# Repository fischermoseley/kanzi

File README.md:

# kanzi
A two wheeled, self balancing skateboard made for a final project in MIT's 6.1311 Power Electronics Laboratory class. Named after Kanzi the Bonobo, because Bonobos are dope.

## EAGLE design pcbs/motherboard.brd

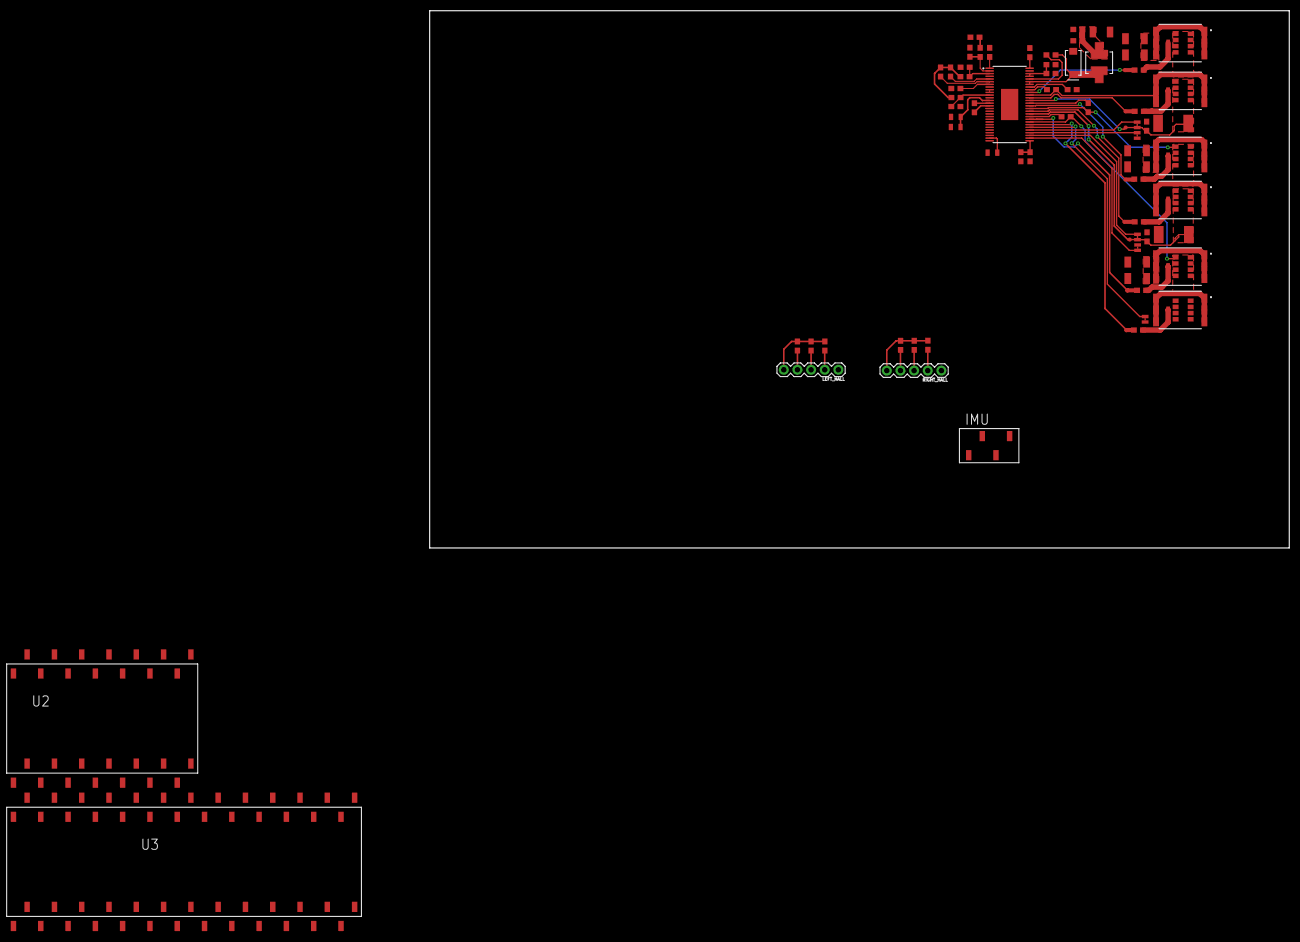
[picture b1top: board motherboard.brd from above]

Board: 2 copper layers, 160.0 x 100.0 mm, 77 parts (0 on the bottom side), 71 nets.

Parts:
C1, C2, C3, C4, C5, C6: 4.7uF 100V; 1210
C7, C8: 1nF; 0603
C9: 6.8nF; 0603
C10: 120pF; 0603
C11, C12, C14: 2.2uF; 0805
C13: 22nF 36V; 0603
C15, C17, C23: 4.7uF; 0603
C16, C18, C19, C20, C21, C22, C24: 0.1uF; 0603
C25: 100uF; 1210
C26: 15nF; 0603
D1: NRVBA2H100T3G; SMA-DIODE
IMU: SSM-104-L-SV; SAMTEC-SSM-104-X-SV
JP1, JP2, JP3, JP4, JP5: JUMPER-SMT_2_NC_TRACE_NO-SILK; SMT-JUMPER_2_NC_TRACE_NO-SILK
L1: 22uH; LQH43
LEFT_HALL: 1X05
R1, R2, R3, R4, R5, R6: 4.7R; 0603
R7, R8: 10mOhm; R2512
R9, R10, R11, R12, R13, R14, R17, R18, R19, R20, R21: 10k; 0603
R15: 200k; 0603
R16: 16.2k; 0603
R22: OPEN; 0603
R23: SHORT; 0603
R24: 1M; 0603
RIGHT_HALL: 1X05
TP1, TP2, TP3, TP4, TP5, TP6, TP7, TP8: TEST-POINT3; PAD.03X.03
U1: DRV8302DCAR; SOP50P810X120-57N
U2: TEENSY3.2
U3: PSOC5LP
U4, U5, U6, U7\, U8, U9: IRF7749L; TRANS_AUIRF8739L2TR

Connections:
+3V3: IMU.3, U2.26
+5V: LEFT_HALL.5, R9.2, R10.2, R11.2, R12.2, R13.2, R14.2, R18.2, R19.2, R20.2, R22.2, RIGHT_HALL.5, U1.9, U1.10, U1.24, U2.28
AGND: C1.2, C2.2, C3.2, C4.2, C5.2, C6.2, C7.2, C8.2, JP2.2, JP4.2, JP5.2, R7.2, R8.2, U9.4, U9.5, U9.6, U9.7, U9.8, U9.9, U9.10, U9.11
DGND: C9.1, C10.1, C11.2, C12.2, C14.2, C15.2, C16.2, C17.2, C18.2, C23.2, C24.2, C25.2, C26.1, D1.A, IMU.4, LEFT_HALL.1, R15.2, R17.1, R21.1, R24.2, RIGHT_HALL.1, U1.8, U1.28, U1.57, U2.1, U3.1, U3.25, U3.51
ENABLE: U1.16, U2.15
GH_A: R1.1, TP1.P$1, U1.47
GH_B: R3.1, TP4.P$1, U1.42
GH_C: R5.1, TP7.P$1, U1.37
GL_A: R2.1, TP2.P$1, U1.45
GL_B: R4.1, TP5.P$1, U1.40
GL_C: R6.1, TP8.P$1, U1.35
LEFT_DIR: U2.9, U3.10
LEFT_FAULT: R19.1, U1.6, U2.24
LEFT_HALL_A: LEFT_HALL.4, R9.1, U2.4, U3.48
LEFT_HALL_B: LEFT_HALL.3, R10.1, U2.5, U3.49
LEFT_HALL_C: LEFT_HALL.2, R11.1, U2.6, U3.50
LEFT_INH_A: U1.17, U3.17
LEFT_INH_B: U1.19, U3.19
LEFT_INH_C: U1.21, U3.21
LEFT_INL_A: U1.18, U3.18
LEFT_INL_B: U1.20, U3.20
LEFT_INL_C: U1.22, U3.22
LEFT_OCTW: R20.1, U1.5, U2.25
LEFT_PWM: U2.7, U3.8
LEFT_SO1: U1.25, U2.19
LEFT_SO2: U1.26, U2.18
unnamed: R15.1, U1.1
unnamed: C9.2, R16.2
unnamed: C10.2, R16.1, U1.2
unnamed: R1.2, U4.12
unnamed: R2.2, U5.12
unnamed: R3.2, U6.12
unnamed: R4.2, U7\.12
unnamed: R5.2, U8.12
unnamed: R6.2, U9.12
unnamed: R17.2, R18.1, U1.3
unnamed: R22.1, R23.2, U1.11
unnamed: C11.1, C12.1, U1.13
unnamed: R21.2, U1.7
unnamed: R23.1, U1.23
unnamed: C13.1, U1.14
unnamed: C13.2, U1.15
unnamed: C14.1, U1.27
unnamed: C15.1, C16.1, U1.29
unnamed: C17.1, C18.1, U1.53, U1.54
unnamed: C19.2, U1.38
unnamed: C20.2, U1.43
unnamed: C21.2, U1.48
unnamed: R24.1, U1.49
unnamed: C22.2, U1.52
unnamed: C22.1, D1.C, L1.1, U1.50, U1.51
unnamed: C23.1, C24.1, C25.1, L1.2
unnamed: C26.2, U1.56
RIGHT_DIR: U2.10, U3.11
RIGHT_HALL_A: R12.1, RIGHT_HALL.4, U2.12, U3.40
RIGHT_HALL_B: R13.1, RIGHT_HALL.3, U2.13, U3.39
RIGHT_HALL_C: R14.1, RIGHT_HALL.2, U2.14, U3.38
RIGHT_PWM: U2.8, U3.9
SCL: IMU.1, U2.21
SDA: IMU.2, U2.20
SH_A: C21.1, U1.46, U4.4, U4.5, U4.6, U4.7, U4.8, U4.9, U4.10, U4.11, U5.1, U5.2, U5.3, U5.13, U5.14, U5.15
SH_B: C20.1, U1.41, U6.4, U6.5, U6.6, U6.7, U6.8, U6.9, U6.10, U6.11, U7\.1, U7\.2, U7\.3, U7\.13, U7\.14, U7\.15
SH_C: C19.1, U1.36, U8.4, U8.5, U8.6, U8.7, U8.8, U8.9, U8.10, U8.11, U9.1, U9.2, U9.3, U9.13, U9.14, U9.15
SL_A: C7.1, JP1.2, R7.1, TP3.P$1, U1.44, U5.4, U5.5, U5.6, U5.7, U5.8, U5.9, U5.10, U5.11
SL_B: C8.1, JP3.2, R8.1, TP6.P$1, U1.39, U7\.4, U7\.5, U7\.6, U7\.7, U7\.8, U7\.9, U7\.10, U7\.11
SL_C: JP5.1, U1.34
SN1: JP1.1, U1.33
SN2: JP3.1, U1.31
SP1: JP2.1, U1.32
SP2: JP4.1, U1.30
VCC: C1.1, C2.1, C3.1, C4.1, C5.1, C6.1, U4.1, U4.2, U4.3, U4.13, U4.14, U4.15, U6.1, U6.2, U6.3, U6.13, U6.14, U6.15, U8.1, U8.2, U8.3, U8.13, U8.14, U8.15

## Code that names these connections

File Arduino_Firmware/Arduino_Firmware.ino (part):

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#define RIGHT_MOTOR_DIR 8

//IO pins to use for interfacing with the hall effect sensors
#define LEFT_HALL_A 2
#define LEFT_HALL_B 3
#define LEFT_HALL_C 4
#define RIGHT_HALL_A 10
#define RIGHT_HALL_B 11
#define RIGHT_HALL_C 12

//Motor configuration
Motor leftMotor, rightMotor;
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
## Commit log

2019-11-13 FVM Working and Arduino Firmware Started
2019-11-15 Added second state machine to PSoC
    Also got hardware working today in lab hehe :smile:
2019-11-17 Added non-hardware based FVM/SVM
2019-11-19 Cleaned up PSoC projects, started making arduino code wait for motor to stop before accelerating
2019-11-19 Moved motor operations into struct
    added functionality for determining if the motor is stopped
2019-11-19 Updated teensy pin definitions, added PSoC code that runs in software, not hardware
2019-11-26 Started layout of final pcb :space_invader:
2019-11-26 Laid out single FET stage
2019-11-30 Cleaned up eagle directory, laid out more of power stage
2019-12-01 Finished first motor channel
2019-12-01 More layout
2019-12-08 Implemented pitch offset in arduino

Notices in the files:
parts and their libraries:
SparkFun-Capacitors: Licensing: Creative Commons ShareAlike 4.0 International - https://creativecommons.org/licenses/by-sa/4.0
